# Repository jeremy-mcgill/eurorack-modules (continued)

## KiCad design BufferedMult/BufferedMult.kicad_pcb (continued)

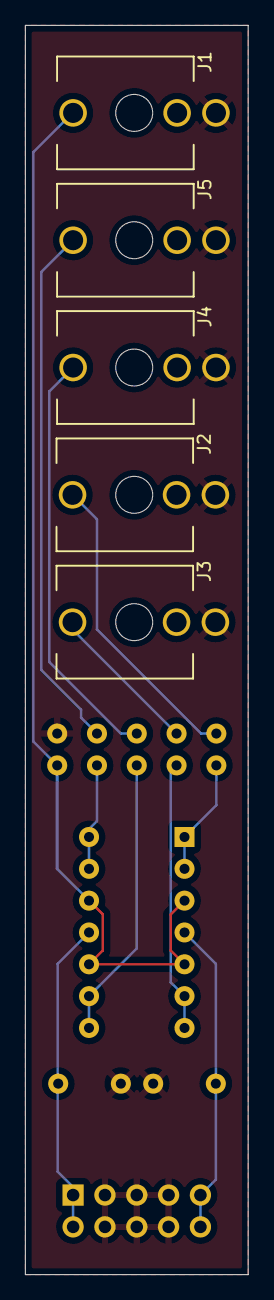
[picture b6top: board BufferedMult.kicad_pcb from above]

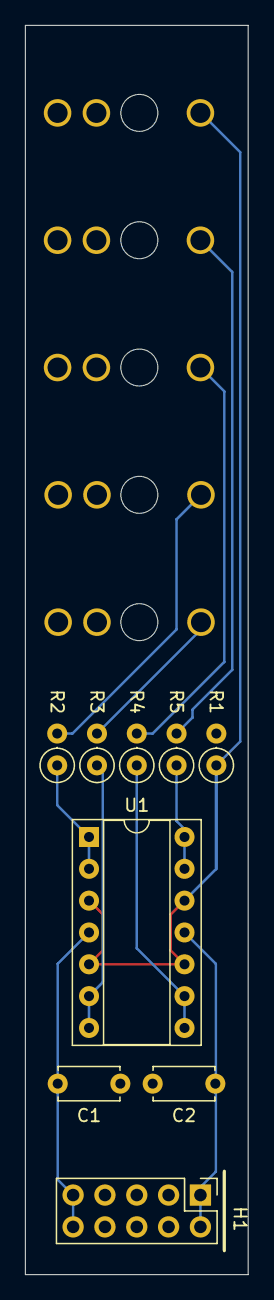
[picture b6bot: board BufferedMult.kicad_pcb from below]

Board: 2 copper layers, 17.8 x 99.7 mm, 14 parts (9 on the bottom side), 12 nets.

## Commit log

2025-03-01 BufferedMult
2025-03-01 Clock
2025-03-01 Clock Front Panel PCB
2025-03-01 Mixer
2025-03-01 PassiveMult
2025-03-01 Sequencer
2025-03-01 Fix footprint for europower connector, add clearance for shrouded connector
2025-03-23 Sequencer progress
2025-03-29 Attenuverter
2025-03-29 Bump Kicad version to 9.0
